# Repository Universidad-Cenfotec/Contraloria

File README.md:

# Proyecto Fiscalización de Obra Pública IoT

Este es el resultado de un proyecto de investigación en coordinación con la Contraloría General de la República de Costa Rica y la cooperación alemana GIZ, para el desarrollo de cámaras IoT de bajo costo, que permitan monitorear y fiscalizar obras de construcción pública, incorporando ideas novedosas para el desarrollo de tecnología local y de bajo costo, además de la utilización de Inteligencia artificial para identificación de patrones de progreso de construcción pública. Este es el repositorio con todos los resultados del proyecto, y que permite su reproducción abierta.

El repositorio del piloto realizado por la contraloría se encuentra en este link:
https://github.com/cgrcostarica/fiscalizacion_infra_IA

## Organización del repositorio
- "code" códigos para los dispositivos utilizados. e instrucciones para programar el microcontrolador
- "design" Archivos 2D y 3D de diseño de estructuras de fabricación y soporte del sistema. Video instruccional de ensamblado de la cámara
- "documentos" Documentación de respaldo (presentaciones, reportes técnicos, documentos de soporte)
- "imagenes" conteien las imágenes que se utilizan en este repositorio
- "placa_tpl" detalles del diseño de la placa TPL, y los esquemas para fabricación

Estes es un proyecto realizado por **Universidad Cenfotec**, en cooperación con la Contraloría General de la República, con fondos de la GIZ.

Aunque exiten tecnologías en el mercado que podría cumplir esta función, este proyecto va dentro de la filosofía "Nuestros para fabricar, adaptar, reparar y crecer", es decir, la intencióne s crear tecnología sobre la cual se pueda evolucionar, y cuyo mejoramiento dependa de nuestras propias acciones y no de la capacidad de un proveedor.

## Investigadores Principales

Dr. Tomás de Camino Beck

Dr. Luis Carlos Naranjo

## Investigadores de apoyo

M.Sc. Rodrigo Herrera

# Asistentes de Investigación y Fabricación

Estudiante Jeffry Valverde

# Etapa de Inteligencia Artificial

**Objetivo:** Crear un modelo de inteligencia artificial que permita realizar la detección de objetos en las imagenes captadas en la etapa de IOT relacionadas al proyecto de contrucción de la Escuela de Pocosi. 

## Investigadores Principales
M.Sc. Rodrigo Herrera

## Asistentes de Investigación y Desarrollo
Gabriel Lobo

Dr. Tomás de Camino Beck

La documentación necesaria de la etapa de IA se encuentra en la carpeta "Documentos Etapa IA-GIZ-CENFOTEC", dentro de la misma contiene la siguiente organización.
- "Códigos" :
  - Los archivos del docker que va en el proceso de producción *sin los modelos
  - El proceso de entrenamiento
  - Autenticación de Google Drive
- "Documentación"
  - La documentación necesaria para todos los procesos
- "Imagenes y Etiquetas
  - Etiquetas necesarias para llevar a cabo el proceso de entrenamiento y evaluación
  - Ejemplo de 5 imagenes
- "Modelos"
  - Contiene un txt que indica donde se puede encontrar los modelos
 
## Resultados de Modelos

Se han compartido 1 modelo principal. 
- Modelo_1_29
  - Metricas
    - Promedio de IoU: 82.7%
    - Sensitividad: 85.4% (Equivale a las predicciones verdaderamente predichas)

### Ejemplo de Inferencia 1

### Ejemplo de Inferencia 2
En este ejemplo se puede observar 2 cajas de diferente color en cada objeto. 

- La caja Azul es la caja de la etiqueta real

- La caja Roja es la caja de la predicción realizada por el modelo

Fácilemente se puede apreciar la efectividad del modelo en hacer su trabajo de predicción. 

### Ejemplo de tabla de resultados
Parte del objetivo es analizar las imagenes que se obtengan por día y de estas obtener un archivo CSV en el cual permita analizar los resultados de una forma ágil y obtener resultados de analísis del monitoreo en las obras. 

En la siguiente imagen se observa un ejemplo del archivo CSV creado de las inferencias realizadas por el modelo, el mismo contiene 4 columnas
- Nombre de la Imagen = imagen analizada
- Clase = predicción de los objetos encontrados
- Probabilidad = probabilidad del objeto encontrado
- Recuadro = las coordenadas necesarias de donde se encontro el objeto en la imagen analizada

*Se debe tomar en cuenta que este modelo esta entrenado solamente con imagenes captadas por las camaras realizadas en la etapa de IoT para el proyecto de construcción de la Escuela de Pocosí, por ende este modelo esta sobre-entrenado para realizar inferencias para este proyecto, en caso de que se ponga el modelo a realizar inferencias de otras imagenes, o proyectos diferentes, es posible que el modelo no sea lo esperado en su eficiencia.

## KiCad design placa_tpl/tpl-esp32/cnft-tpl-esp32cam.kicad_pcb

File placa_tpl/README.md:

# Placa TPL para ESP32CAM

Shield para cámara ESP32CAM, con chip TPL para fotos a intervalos y bajo consumo de batería. Diseñado por Tomás de Camino Beck, con ayuda de CrCibernetica.com, para poryecto GIZ-CGR-Universidad Cenfotec.

Para actualizciones de esta placa puede revisar [este repositorio](https://github.com/CRCibernetica/cnft-tpl-esp32cam)

# Prototipado de la placa

La placa se desarrolla a partir del chip TPL5110.  En la fotografía se muestra 1. Pruebas breadboard, 2. fabricado protoboard, 3. placa final fabricada en china

# Breadboard

Utilizando el TPL5110 de Adafruir puede construir el circuito en un breadboard siguiendo el siguiente esquema:

Nota: El capacitor puede variar depediendo de la batería que se utilice. Para este proyecto se utilizó 47uF 16v

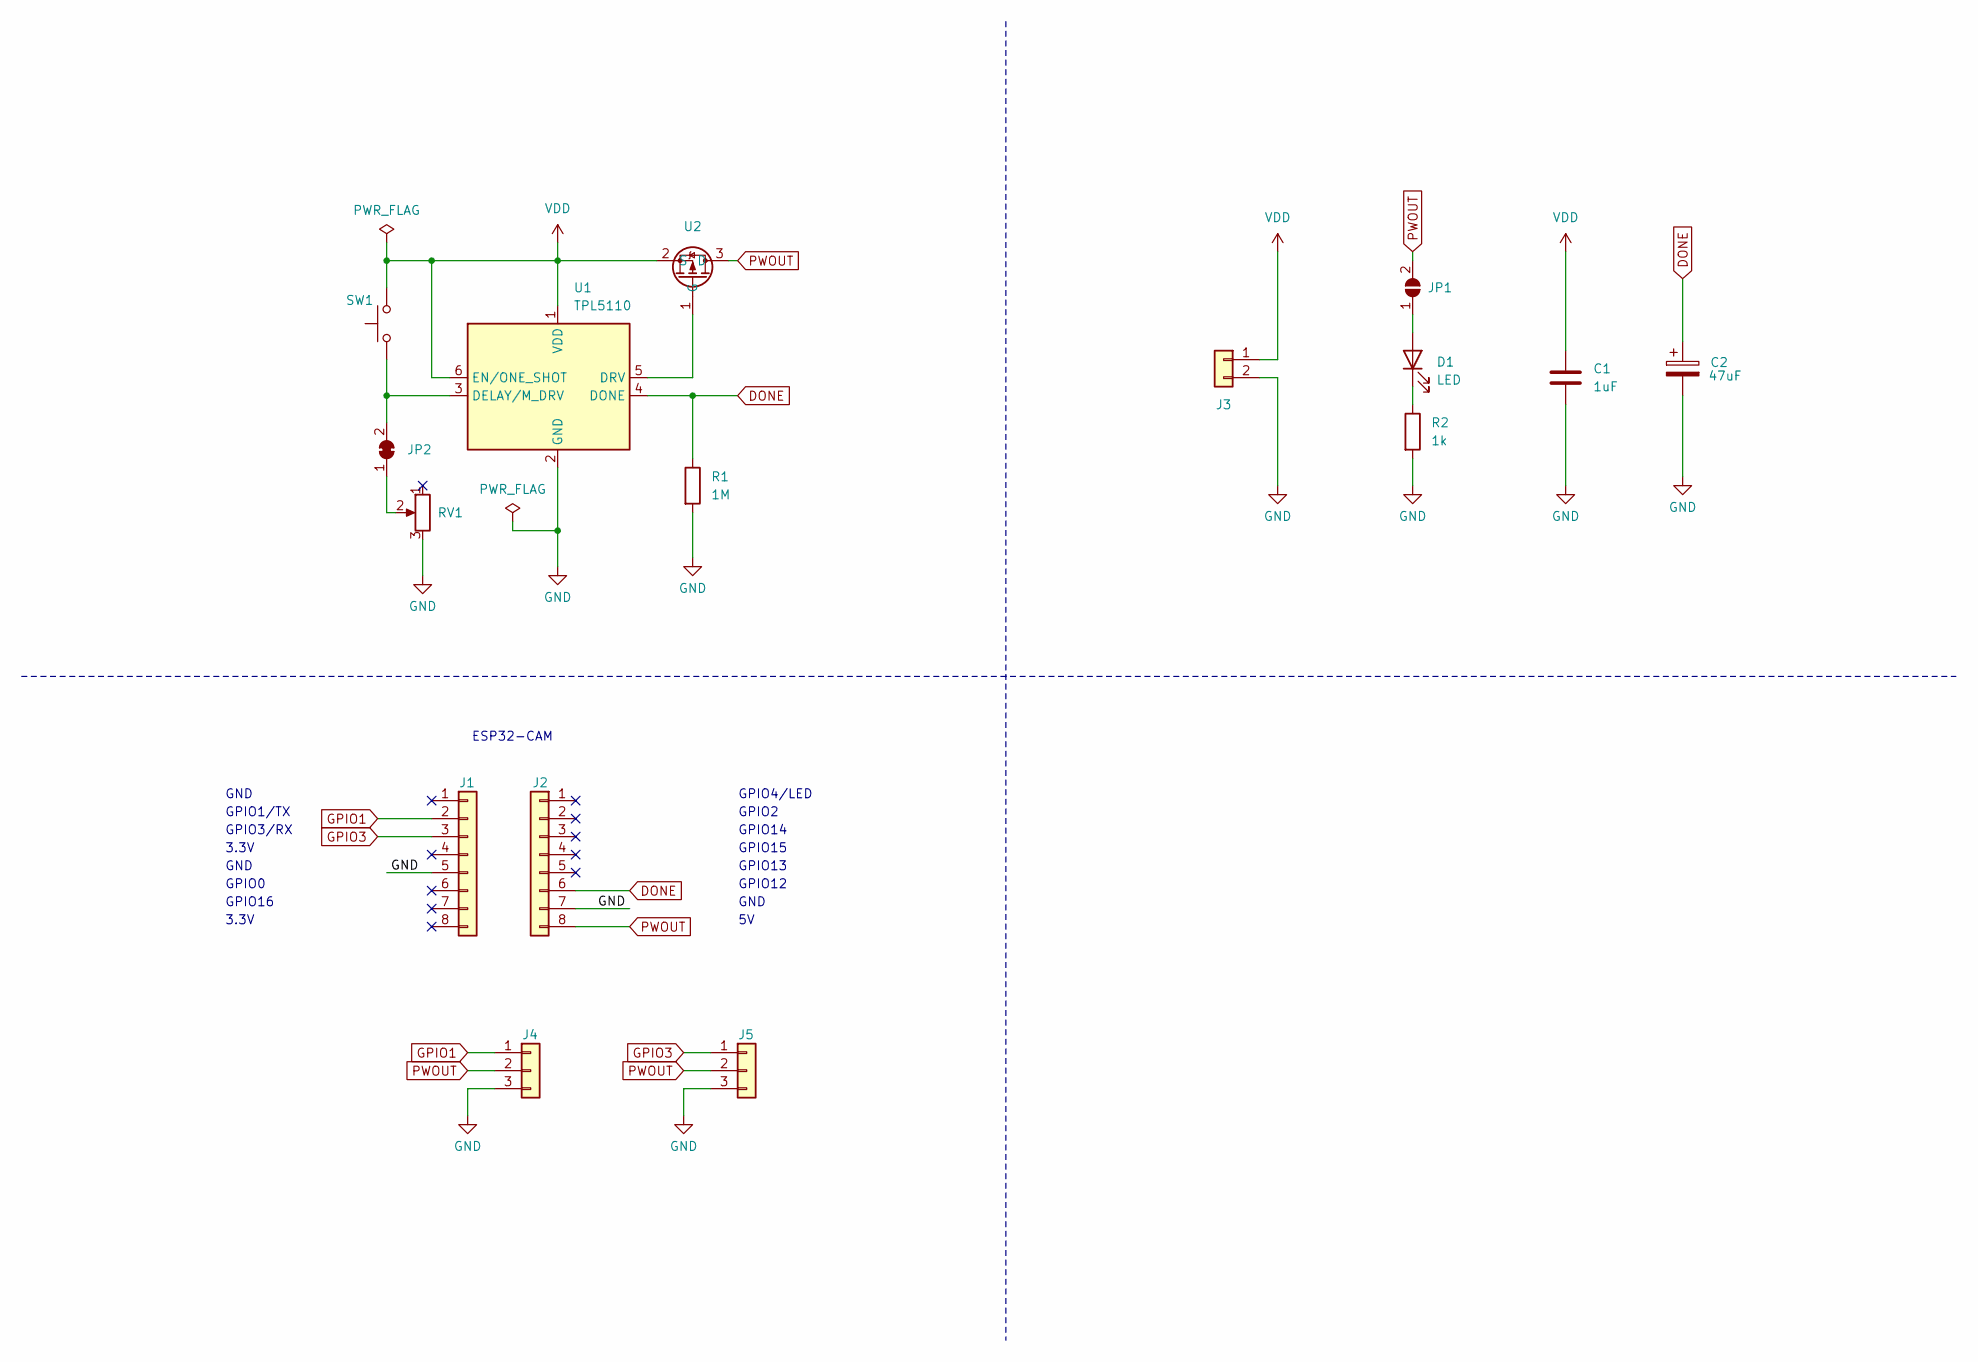
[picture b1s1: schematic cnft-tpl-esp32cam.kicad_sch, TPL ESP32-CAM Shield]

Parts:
C1: 1uF; C_0805_2012Metric
C2: 47uF; CP_Elec_5x5.4
D1: LED; LED_0603_1608Metric
J1, J2: Conn_01x08; PinSocket_1x08_P2.54mm_Vertical
J3: Conn_01x02; JST_PH_B2B-PH-SM4-TB_1x02-1MP_P2.00mm_Vertical
J4, J5: Conn_01x03; PinHeader_1x03_P2.54mm_Vertical
JP1: SolderJumper_2_Open; SolderJumper-2_P1.3mm_Open_RoundedPad1.0x1.5mm
JP2: SolderJumper_2_Bridged; SolderJumper-2_P1.3mm_Bridged_RoundedPad1.0x1.5mm
R1: 1M; R_0805_2012Metric
R2: 1k; R_0805_2012Metric
RV1: 200k; Potentiometer_Bourns_TC33X_Vertical
SW1: SW_Push; SKRKAEE020
U1: TPL5110; TSOT-23-6
U2: DMG3415; SOT-23

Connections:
DONE: C2.1, J2.6, R1.1, U1.4 (DONE)
GND: C1.2, C2.2, J1.5, J2.7, J3.2, J4.3, J5.3, R1.2, R2.2, RV1.3, U1.2 (GND)
GPIO1: J1.2, J4.1
GPIO3: J1.3, J5.1
unnamed: D1.2 (A), JP1.1 (A)
unnamed: D1.1 (K), R2.1
unnamed: JP2.1 (A), RV1.2
unnamed: JP2.2 (B), SW1.1, U1.3 (DELAY/M_DRV)
unnamed: U1.5 (DRV), U2.1 (G)
PWOUT: J2.8, J4.2, J5.2, JP1.2 (B), U2.3 (D)
VDD: C1.1, J3.1, SW1.2, U1.1 (VDD), U1.6 (EN/ONE_SHOT), U2.2 (S)

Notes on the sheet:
GND
GPIO13
GPIO12
GPIO0
GPIO4/LED
GPIO15
GPIO16
3.3V
GPIO2
ESP32-CAM
GPIO3/RX
GPIO14
GPIO1/TX

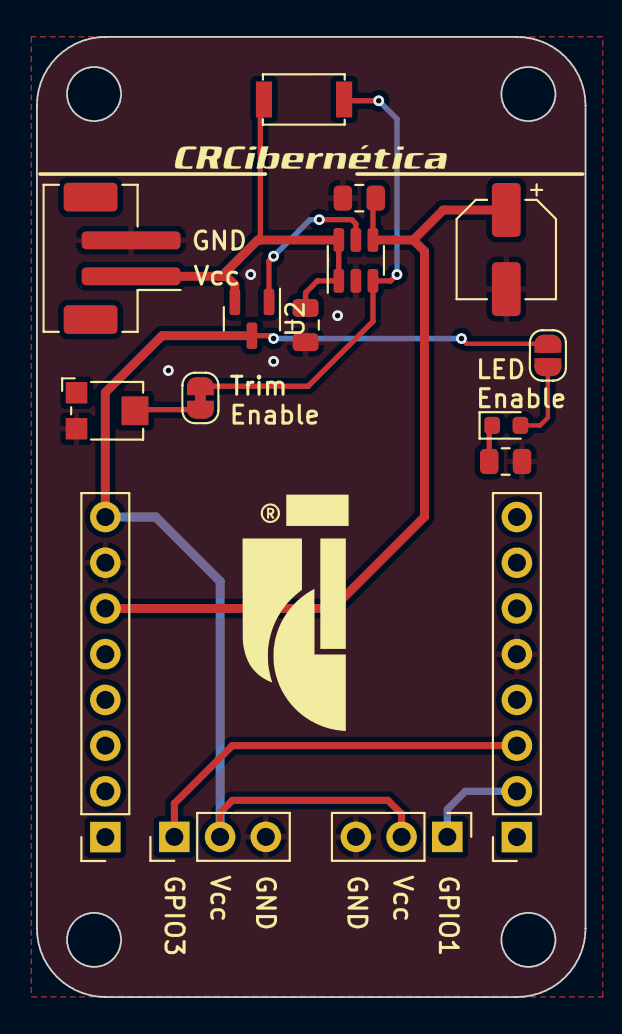
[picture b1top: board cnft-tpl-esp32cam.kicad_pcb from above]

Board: 2 copper layers, 30.5 x 53.3 mm, 16 parts (0 on the bottom side), 11 nets.

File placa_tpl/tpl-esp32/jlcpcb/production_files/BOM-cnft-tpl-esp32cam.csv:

Comment,Designator,Footprint,LCSC
SW_Push,SW1,SKRKAEE020,C115357
TPL5110,U1,TSOT-23-6,C125830
200k,RV1,Potentiometer_Bourns_TC33X_Vertical,C128551
Conn_01x02,J3,JST_PH_B2B-PH-SM4-TB_1x02-1MP_P2.00mm_Vertical,C160352
1k,R2,R_0805_2012Metric,C25623
1M,R1,R_0805_2012Metric,C26115
1uF,C1,C_0805_2012Metric,C28323
Conn_01x08,"J1,J2",PinSocket_1x08_P2.54mm_Vertical,C2897371
LED,D1,LED_0603_1608Metric,C434423
47uF,C2,CP_Elec_5x5.4,C4747957
Conn_01x03,"J4,J5",PinHeader_1x03_P2.54mm_Vertical,C492411
DMG3415,U2,SOT-23,C96616

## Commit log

2023-10-25 Captura y carga de fotos con ESP32-CAM
    Agrega el código necesario para capturar fotos automáticamente cada minuto utilizando una cámara ESP32-CAM y cargarlas de inmediato a Google Drive. Esto permitirá la monitorización y grabación periód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
2023-10-25 Script Google Drive
    Permite la configuración de Google Drive para recibir las fotos enviadas desde la ESP32-CAM.
2023-10-25 Explicación README.md
2023-10-31 esp32-cam deepsleep
2023-11-01 esp32-cam deep sleep
2024-04-08 Delete Design/Box_Camera_V1.stl
    Obsoleto
2024-04-08 Delete Design/Camera_Box_Full.stl
    Obsoleto
2024-04-08 Delete Design/Camera_Box2_3.stl
    Obsoleto
2024-04-08 Update README.md
    Actualización de archivos de impresión 3D, con versión final
2024-04-08 Update README.md
    Cambio de título
2024-04-10 Update README.md
    Descripción de código
2024-04-29 Add files via upload
    Presentaciones realizadas durante el proyecto
2024-04-29 Rename Avances 2 (1).pdf to Avances 2.pdf
2024-05-03 Create prueba de lnaranjo
2024-05-03 Update README.md
    Agregado de instrucciones de Arduino IDE
2024-05-03 Update README.md
    Instrucciones de creación de acceso a google drive
2024-05-07 Documentacion IA
2024-05-07 inferencia
2024-05-08 modelos
2024-05-08 actualizar nombre modelo
2024-05-09 Presentaciones
